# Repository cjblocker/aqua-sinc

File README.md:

# AquaSinc

A small home-made aquarium controller built around an ARM Cortex M4 STM32f and a Raspberry Pi

## Reference

- 1Bitsy Pinout [ https://github.com/esden/1BitSy ]

## Parts
- 3.3V LDO [ https://www.arrow.com/en/products/mcp1703a-3302edb/microchip-technology ]
- Green Chip LED [ https://www.arrow.com/en/products/kpg-1608vgc-a/kingbright ]

## Dev Instructions for Black Magic Probe

Putting these here because I forget...

1. `$ arm-none-eabi-gdb src/main.elf` or `make debug`
    Upon start up of gdb, these should automatically be exectured from .gdbinit
    ```bash
    (gdb) set target-async on
    (gdb) set confirm off
    (gdb) set mem inaccessible-by-default off
    (gdb) target extended-remote /dev/cu.usbmodem7BAB88A81
    (gdb) monitor version
    (gdb) monitor swdp_scan
    (gdb) attach 1
    ```
2. Load the program from the connected computer with `load`
3. Use any of the following to debug
    * `run` - start or restart the program
    * `start` - run till the beginning of the main function, restart if needed
    * `Ctrl-C` - interrupt the program while running
    * `continue` - resume running after being stopped
    * `next` - run next line of program (but don't step into functions)
    * `step` - like next, but steps into a function
    * `finish` - run till you leave the current function
    * `list [line number]` - show 10 lines surrounding [line number], current line by default
    * `info locals` - print out local variables
    * `set variable <var_name>=<value>` - set variable _var_name_ to _value_
    * `break <line_number>` - set a breakpoint at _line_number_
    * `info breakpoints` - list current breakpoints
    * `disable breakpoints`
    * `delete breakpoints`
    * `watch <var_name>` - set a watchpoint on variable _var_name_
    * `print <expression>` - evaluates expression and prints it
    * `printf <format_string>,<var_name>` - place _var_name_ in the format string at points with %d,%s,etc
    * `commands ... end` - execute the given commands after the previously created watchpoint is changed. 
        Example:
        ```bash
        (gdb) watch blink_count
        (gdb) commands
        > printf "blink extend condition %d\n", blink_count^4
        > end
        ```
4. If you make changes to main.c, you can run make from within gdb, followed by `load`.
5. `quit` to exit gdb or `Ctrl-D`

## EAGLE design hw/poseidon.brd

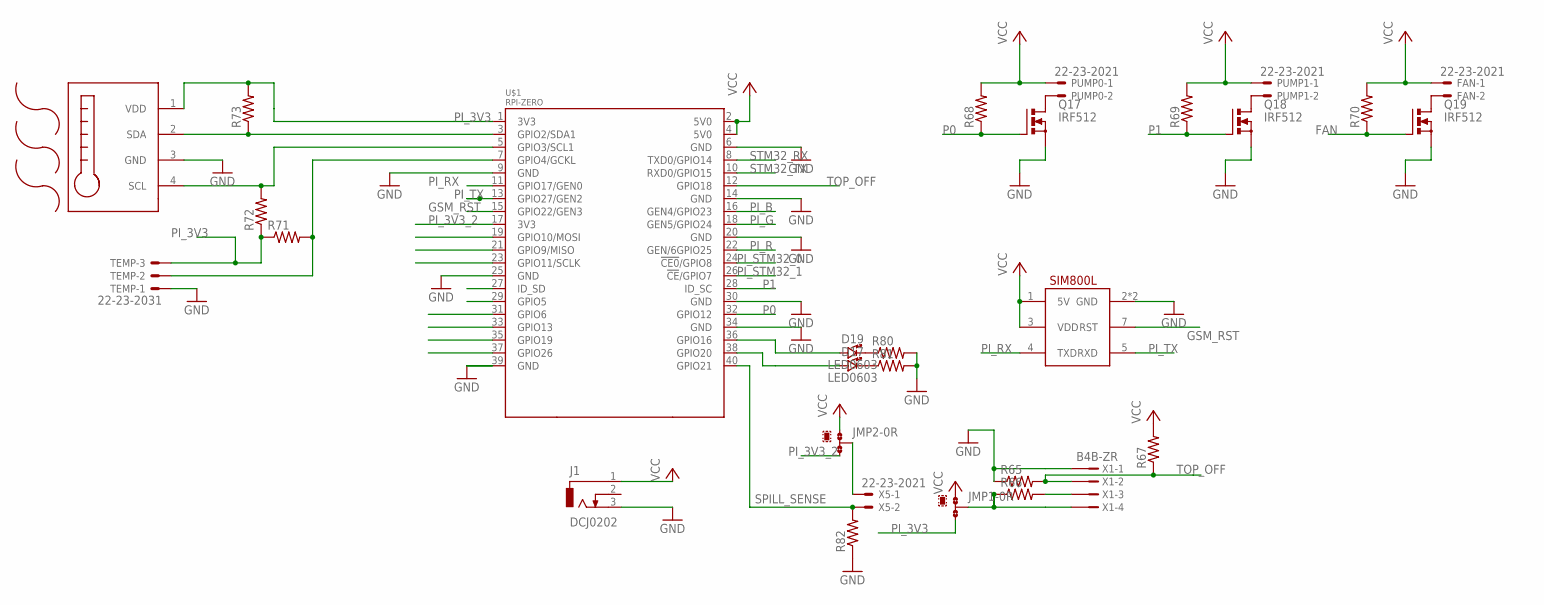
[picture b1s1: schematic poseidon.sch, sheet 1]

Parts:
D17, D19: LED0603; LED-0603
FAN: 22-23-2021
J1: DCJ0202
JMP1, JMP2: 0R-JUMPA; A0R-JMP
PUMP0, PUMP1: 22-23-2021
Q17, Q18, Q19: IRF512; TO220BV
R65, R66, R68, R69, R70, R71, R72, R73, R80, R81, R82: R-US_R0805; R0805
R67: R-US_M0805; M0805
TEMP: 22-23-2031
U$1: RPI-ZERO; RASPBERRYPI_BASTELSTUBE_V13_RASPI_BOARD_B+_FULL
U$3: AM2320; 4PIN_SMD
U$21: SIM800L; SIP
X1: B4B-ZR
X5: 22-23-2021

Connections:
FAN: Q19.G, R70.1; also elsewhere on the board
GND: J1.3, Q17.S, Q18.S, Q19.S, R65.1, R80.2, R81.2, R82.1, TEMP.1, U$1.6 (GND), U$1.9 (GND), U$1.14 (GND), U$1.20 (GND), U$1.25 (GND), U$1.30 (GND), U$1.34 (GND), U$1.39 (GND), U$3.3 (GND), U$21.2 (GND), U$21.6 (GND), X1.1; also elsewhere on the board
GSM_RST: U$1.15 (GPIO22/GEN3), U$21.7 (RST)
unnamed: PUMP0.2, Q17.D
unnamed: D19.C (CATHODE), R80.1
unnamed: R66.2, X1.3
unnamed: JMP1.2, R66.1, X1.4
unnamed: PUMP1.2, Q18.D
unnamed: D17.C (CATHODE), R81.1
unnamed: FAN.2, Q19.D
unnamed: R71.2, TEMP.2, U$1.7 (GPIO4/GCKL)
unnamed: R73.1, U$1.3 (GPIO2/SDA1), U$3.2 (SDA)
unnamed: R72.2, U$1.5 (GPIO3/SCL1), U$3.4 (SCL)
unnamed: D19.A (ANODE), U$1.36 (GPIO16)
unnamed: D17.A (ANODE), U$1.38 (GPIO20)
unnamed: JMP2.2, X5.1
P0: Q17.G, R68.1, U$1.32 (GPIO12)
P1: Q18.G, R69.1, U$1.28 (ID_SC)
PI_3V3: JMP1.3, R71.1, R72.1, R73.2, TEMP.3, U$1.1 (3V3), U$3.1 (VDD); also elsewhere on the board
PI_3V3_2: JMP2.3, U$1.17 (3V3)
PI_B: U$1.16 (GEN4/GPIO23); also elsewhere on the board
PI_G: U$1.18 (GEN5/GPIO24); also elsewhere on the board
PI_R: U$1.22 (GEN/6GPIO25); also elsewhere on the board
PI_RX: U$1.11 (GPIO17/GEN0), U$21.4 (TXD)
PI_STM32_0: U$1.24 (!CE0!/GPIO8); also elsewhere on the board
PI_STM32_1: U$1.26 (!CE!/GPIO7); also elsewhere on the board
PI_TX: U$1.13 (GPIO27/GEN2), U$21.5 (RXD)
SPILL_SENSE: R82.2, U$1.40 (GPIO21), X5.2
STM32_RX: U$1.8 (TXD0/GPIO14); also elsewhere on the board
STM32_TX: U$1.10 (RXD0/GPIO15); also elsewhere on the board
TOP_OFF: R65.2, R67.1, U$1.12 (GPIO18), X1.2
VCC: FAN.1, J1.1, JMP1.1, JMP2.1, PUMP0.1, PUMP1.1, R67.2, R68.2, R69.2, R70.2, U$1.2 (5V0), U$1.4 (5V0), U$21.1 (5V), U$21.3 (VDD); also elsewhere on the board

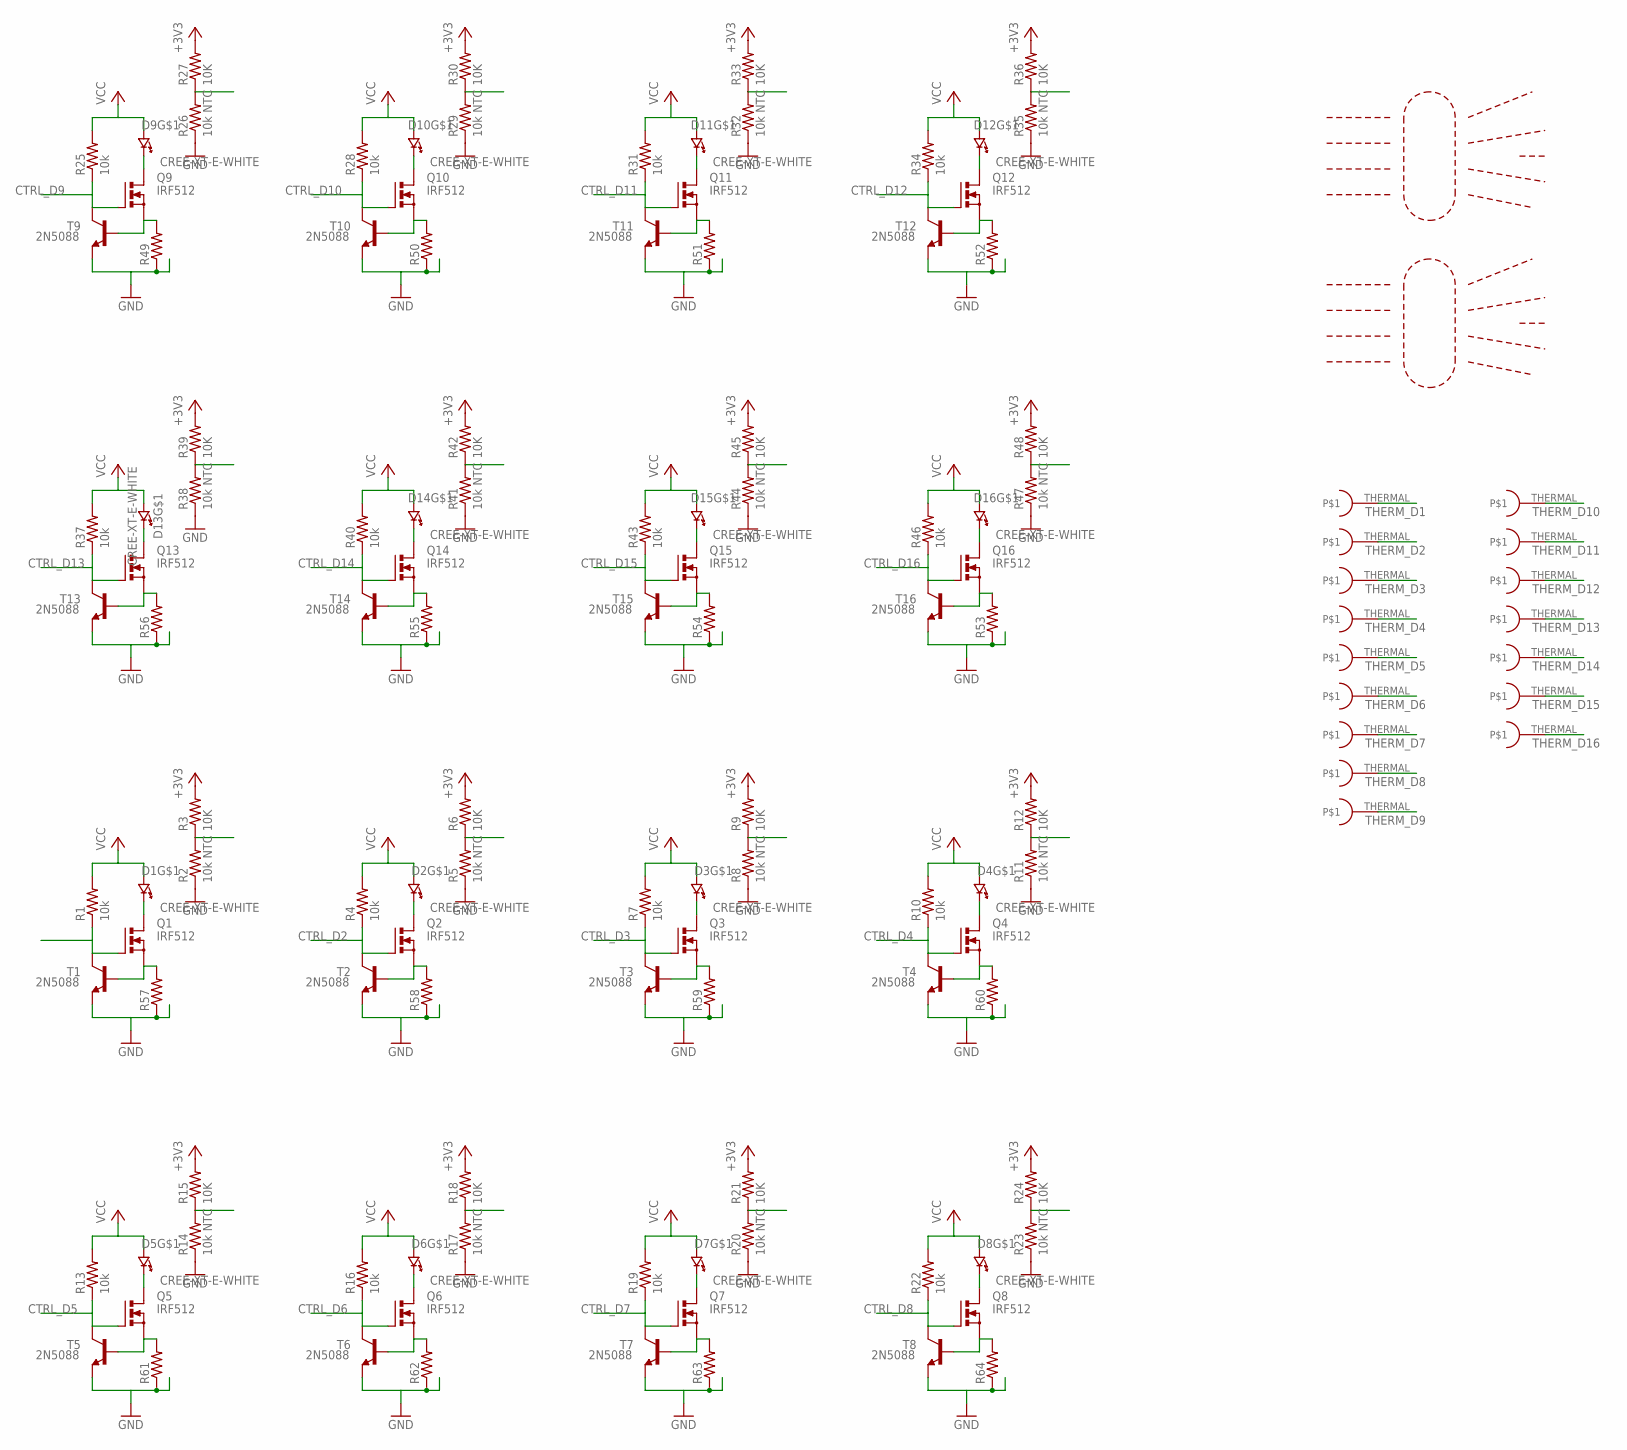
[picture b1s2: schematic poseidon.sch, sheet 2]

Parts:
D1, D2, D3, D4, D5, D6, D7, D8, D9, D10, D11, D12, D13, D14, D15, D16: CREE-XT-E-WHITE; CREE-XT-E
Q1, Q2, Q3, Q4, Q5, Q6, Q7, Q8, Q9, Q10, Q11, Q12, Q13, Q14, Q15, Q16: IRF512; TO220BV
R1, R4, R7, R10, R13, R16, R19, R22, R25, R28, R31, R34, R37, R40, R43, R46: 10k; R0805
R2, R5, R8, R11, R14, R17, R20, R23, R26, R29, R32, R35, R38, R41, R44, R47: 10k NTC; R0805
R3, R6, R9, R12, R15, R18, R21, R24, R27, R30, R33, R36, R39, R42, R45, R48: 10K; R0603
R49, R50, R51, R52, R53, R54, R55, R56, R57, R58, R59, R60, R61, R62, R63, R64: R-US_R2512; R2512
T1, T2, T3, T4, T5, T6, T7, T8, T9, T10, T11, T12, T13, T14, T15, T16: 2N5088; TO92
U$19, U$20: 8X_LED_OPTIC; FOCUS_GRID

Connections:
+3V3: R3.2, R6.2, R9.2, R12.2, R15.2, R18.2, R21.2, R24.2, R27.2, R30.2, R33.2, R36.2, R39.2, R42.2, R45.2, R48.2; also elsewhere on the board
CTRL_D1: Q1.G, R1.1, T1.1 (C); also elsewhere on the board
CTRL_D2: Q2.G, R4.1, T2.1 (C); also elsewhere on the board
CTRL_D3: Q3.G, R7.1, T3.1 (C); also elsewhere on the board
CTRL_D4: Q4.G, R10.1, T4.1 (C); also elsewhere on the board
CTRL_D5: Q5.G, R13.1, T5.1 (C); also elsewhere on the board
CTRL_D6: Q6.G, R16.1, T6.1 (C); also elsewhere on the board
CTRL_D7: Q7.G, R19.1, T7.1 (C); also elsewhere on the board
CTRL_D8: Q8.G, R22.1, T8.1 (C); also elsewhere on the board
CTRL_D9: Q9.G, R25.1, T9.1 (C); also elsewhere on the board
CTRL_D10: Q10.G, R28.1, T10.1 (C); also elsewhere on the board
CTRL_D11: Q11.G, R31.1, T11.1 (C); also elsewhere on the board
CTRL_D12: Q12.G, R34.1, T12.1 (C); also elsewhere on the board
CTRL_D13: Q13.G, R37.1, T13.1 (C); also elsewhere on the board
CTRL_D14: Q14.G, R40.1, T14.1 (C); also elsewhere on the board
CTRL_D15: Q15.G, R43.1, T15.1 (C); also elsewhere on the board
CTRL_D16: Q16.G, R46.1, T16.1 (C); also elsewhere on the board
GND: R2.1, R5.1, R8.1, R11.1, R14.1, R17.1, R20.1, R23.1, R26.1, R29.1, R32.1, R35.1, R38.1, R41.1, R44.1, R47.1, R49.1, R50.1, R51.1, R52.1, R53.1, R54.1, R55.1, R56.1, R57.1, R58.1, R59.1, R60.1, R61.1, R62.1, R63.1, R64.1, T1.3 (E), T2.3 (E), T3.3 (E), T4.3 (E), T5.3 (E), T6.3 (E), T7.3 (E), T8.3 (E), T9.3 (E), T10.3 (E), T11.3 (E), T12.3 (E), T13.3 (E), T14.3 (E), T15.3 (E), T16.3 (E); also elsewhere on the board
unnamed: D1.K (CATHODE), Q1.D
unnamed: Q1.S, R57.2, T1.2 (B)
unnamed: D2.K (CATHODE), Q2.D
unnamed: Q2.S, R58.2, T2.2 (B)
unnamed: D3.K (CATHODE), Q3.D
unnamed: Q3.S, R59.2, T3.2 (B)
unnamed: D4.K (CATHODE), Q4.D
unnamed: Q4.S, R60.2, T4.2 (B)
unnamed: D5.K (CATHODE), Q5.D
unnamed: Q5.S, R61.2, T5.2 (B)
unnamed: D6.K (CATHODE), Q6.D
unnamed: Q6.S, R62.2, T6.2 (B)
unnamed: D7.K (CATHODE), Q7.D
unnamed: Q7.S, R63.2, T7.2 (B)
unnamed: D8.K (CATHODE), Q8.D
unnamed: Q8.S, R64.2, T8.2 (B)
unnamed: D9.K (CATHODE), Q9.D
unnamed: Q9.S, R49.2, T9.2 (B)
unnamed: D10.K (CATHODE), Q10.D
unnamed: Q10.S, R50.2, T10.2 (B)
unnamed: D11.K (CATHODE), Q11.D
unnamed: Q11.S, R51.2, T11.2 (B)
unnamed: D12.K (CATHODE), Q12.D
unnamed: Q12.S, R52.2, T12.2 (B)
unnamed: D13.K (CATHODE), Q13.D
unnamed: Q13.S, R56.2, T13.2 (B)
unnamed: D14.K (CATHODE), Q14.D
unnamed: Q14.S, R55.2, T14.2 (B)
unnamed: D15.K (CATHODE), Q15.D
unnamed: Q15.S, R54.2, T15.2 (B)
unnamed: D16.K (CATHODE), Q16.D
unnamed: Q16.S, R53.2, T16.2 (B)
TEMP_D1: R41.2, R42.1; also elsewhere on the board
TEMP_D2: R8.2, R9.1; also elsewhere on the board
TEMP_D3: R14.2, R15.1; also elsewhere on the board
TEMP_D4: R17.2, R18.1; also elsewhere on the board
TEMP_D5: R44.2, R45.1; also elsewhere on the board
TEMP_D6: R47.2, R48.1; also elsewhere on the board
TEMP_D7: R11.2, R12.1; also elsewhere on the board
TEMP_D8: R20.2, R21.1; also elsewhere on the board
TEMP_D9: R32.2, R33.1; also elsewhere on the board
TEMP_D10: R29.2, R30.1; also elsewhere on the board
TEMP_D11: R26.2, R27.1; also elsewhere on the board
TEMP_D12: R23.2, R24.1; also elsewhere on the board
TEMP_D13: R5.2, R6.1; also elsewhere on the board
TEMP_D14: R35.2, R36.1; also elsewhere on the board
TEMP_D15: R38.2, R39.1; also elsewhere on the board
TEMP_D16: R2.2, R3.1; also elsewhere on the board
THERM_D1: D1.THERMAL
THERM_D2: D2.THERMAL
THERM_D3: D3.THERMAL
THERM_D4: D4.THERMAL
THERM_D5: D5.THERMAL
THERM_D6: D6.THERMAL
THERM_D7: D7.THERMAL
THERM_D8: D8.THERMAL
THERM_D9: D9.THERMAL
THERM_D10: D10.THERMAL
THERM_D11: D11.THERMAL
THERM_D12: D12.THERMAL
THERM_D13: D13.THERMAL
THERM_D14: D14.THERMAL
THERM_D15: D15.THERMAL
THERM_D16: D16.THERMAL
VCC: D1.A (ANODE), D2.A (ANODE), D3.A (ANODE), D4.A (ANODE), D5.A (ANODE), D6.A (ANODE), D7.A (ANODE), D8.A (ANODE), D9.A (ANODE), D10.A (ANODE), D11.A (ANODE), D12.A (ANODE), D13.A (ANODE), D14.A (ANODE), D15.A (ANODE), D16.A (ANODE), R1.2, R4.2, R7.2, R10.2, R13.2, R16.2, R19.2, R22.2, R25.2, R28.2, R31.2, R34.2, R37.2, R40.2, R43.2, R46.2; also elsewhere on the board

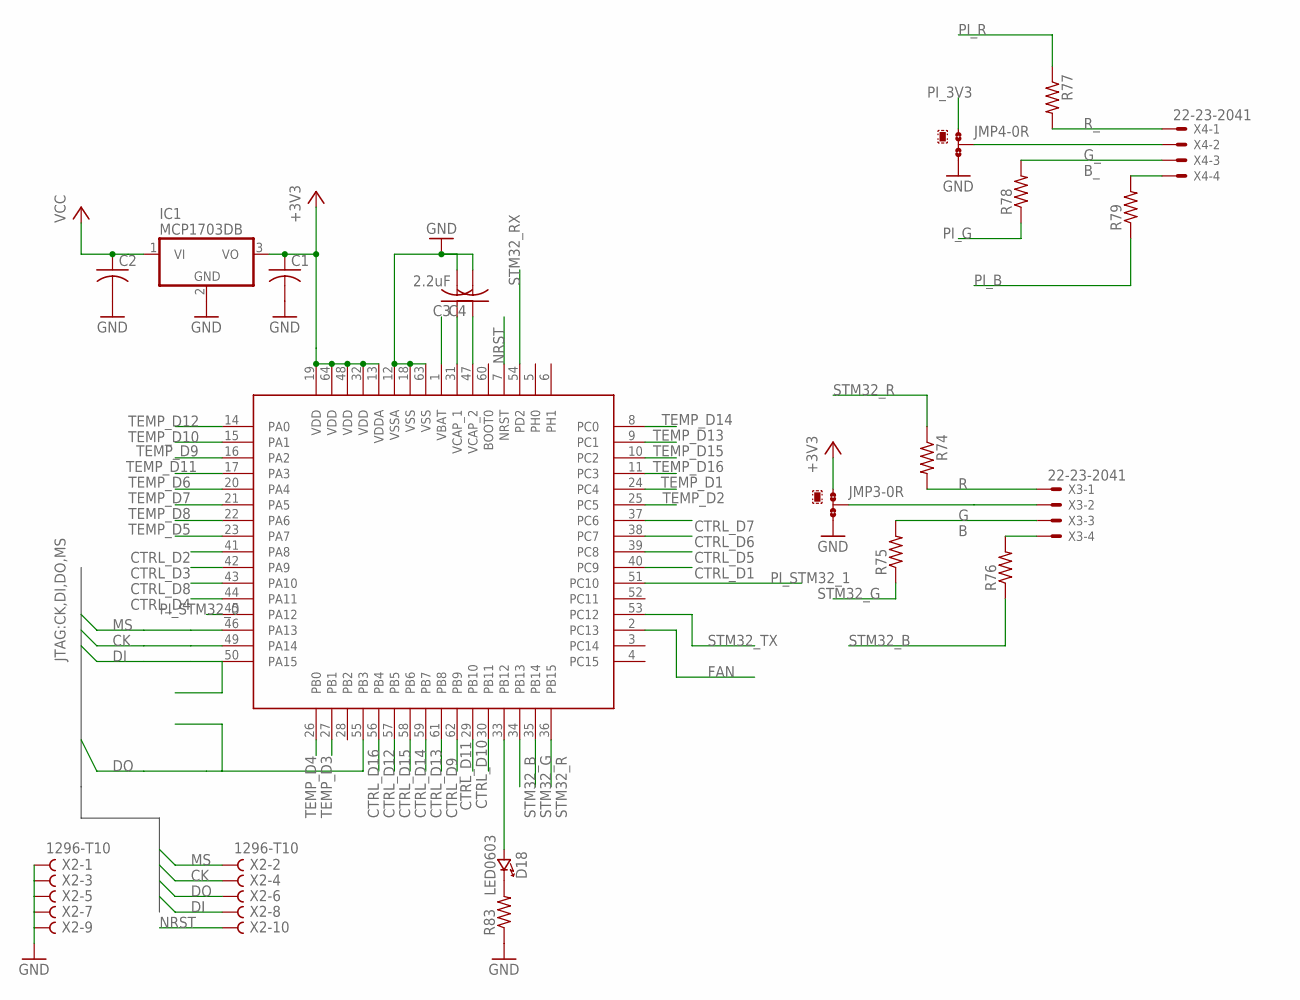
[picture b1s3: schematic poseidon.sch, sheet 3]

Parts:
C1, C2: C-USC0805; C0805
C3: 2.2uF; C0402K
C4: C-USC0402K; C0402K
D18: LED0603; LED-0603
IC1: MCP1703DB; SOT223
JMP3, JMP4: 0R-JUMPA; A0R-JMP
R74, R75, R76, R77, R78, R79, R83: R-US_R0805; R0805
U$2: STM32F41; QFP50P1200X1200X160-64
X2: 1296-T10; 1296-10
X3, X4: 22-23-2041

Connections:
+3V3: C1.1, IC1.3 (VO), JMP3.1, U$2.13 (VDDA), U$2.19 (VDD), U$2.32 (VDD), U$2.48 (VDD), U$2.64 (VDD); also elsewhere on the board
B: R76.2, X3.4
B_: R79.2, X4.4
CK: U$2.49 (PA14), X2.4
CTRL_D1: U$2.40 (PC9); also elsewhere on the board
CTRL_D2: U$2.41 (PA8); also elsewhere on the board
CTRL_D3: U$2.42 (PA9); also elsewhere on the board
CTRL_D4: U$2.44 (PA11); also elsewhere on the board
CTRL_D5: U$2.39 (PC8); also elsewhere on the board
CTRL_D6: U$2.38 (PC7); also elsewhere on the board
CTRL_D7: U$2.37 (PC6); also elsewhere on the board
CTRL_D8: U$2.43 (PA10); also elsewhere on the board
CTRL_D9: U$2.62 (PB9); also elsewhere on the board
CTRL_D10: U$2.30 (PB11); also elsewhere on the board
CTRL_D11: U$2.29 (PB10); also elsewhere on the board
CTRL_D12: U$2.57 (PB5); also elsewhere on the board
CTRL_D13: U$2.61 (PB8); also elsewhere on the board
CTRL_D14: U$2.59 (PB7); also elsewhere on the board
CTRL_D15: U$2.58 (PB6); also elsewhere on the board
CTRL_D16: U$2.56 (PB4); also elsewhere on the board
DI: U$2.50 (PA15), X2.8
DO: U$2.55 (PB3), X2.6
FAN: U$2.2 (PC13); also elsewhere on the board
G: R75.2, X3.3
GND: C1.2, C2.2, C3.2, C4.2, IC1.2 (GND), JMP3.3, JMP4.3, R83.1, U$2.12 (VSSA), U$2.18 (VSS), U$2.63 (VSS), X2.1, X2.3, X2.5, X2.7, X2.9; also elsewhere on the board
G_: R78.2, X4.3
MS: U$2.46 (PA13), X2.2
unnamed: JMP4.2, X4.2
unnamed: JMP3.2, X3.2
unnamed: D18.C (CATHODE), R83.2
unnamed: D18.A (ANODE), U$2.33 (PB12)
unnamed: C3.1, U$2.31 (VCAP_1)
unnamed: C4.1, U$2.47 (VCAP_2)
NRST: U$2.7 (NRST), X2.10
PI_3V3: JMP4.1; also elsewhere on the board
PI_B: R79.1; also elsewhere on the board
PI_G: R78.1; also elsewhere on the board
PI_R: R77.1; also elsewhere on the board
PI_STM32_0: U$2.45 (PA12); also elsewhere on the board
PI_STM32_1: U$2.51 (PC10); also elsewhere on the board
R: R74.2, X3.1
R_: R77.2, X4.1
STM32_B: R76.1, U$2.34 (PB13)
STM32_G: R75.1, U$2.35 (PB14)
STM32_R: R74.1, U$2.36 (PB15)
STM32_RX: U$2.54 (PD2); also elsewhere on the board
STM32_TX: U$2.53 (PC12); also elsewhere on the board
TEMP_D1: U$2.24 (PC4); also elsewhere on the board
TEMP_D2: U$2.25 (PC5); also elsewhere on the board
TEMP_D3: U$2.27 (PB1); also elsewhere on the board
TEMP_D4: U$2.26 (PB0); also elsewhere on the board
TEMP_D5: U$2.23 (PA7); also elsewhere on the board
TEMP_D6: U$2.20 (PA4); also elsewhere on the board
TEMP_D7: U$2.21 (PA5); also elsewhere on the board
TEMP_D8: U$2.22 (PA6); also elsewhere on the board
TEMP_D9: U$2.16 (PA2); also elsewhere on the board
TEMP_D10: U$2.15 (PA1); also elsewhere on the board
TEMP_D11: U$2.17 (PA3); also elsewhere on the board
TEMP_D12: U$2.14 (PA0); also elsewhere on the board
TEMP_D13: U$2.9 (PC1); also elsewhere on the board
TEMP_D14: U$2.8 (PC0); also elsewhere on the board
TEMP_D15: U$2.10 (PC2); also elsewhere on the board
TEMP_D16: U$2.11 (PC3); also elsewhere on the board
VCC: C2.1, IC1.1 (VI); also elsewhere on the board

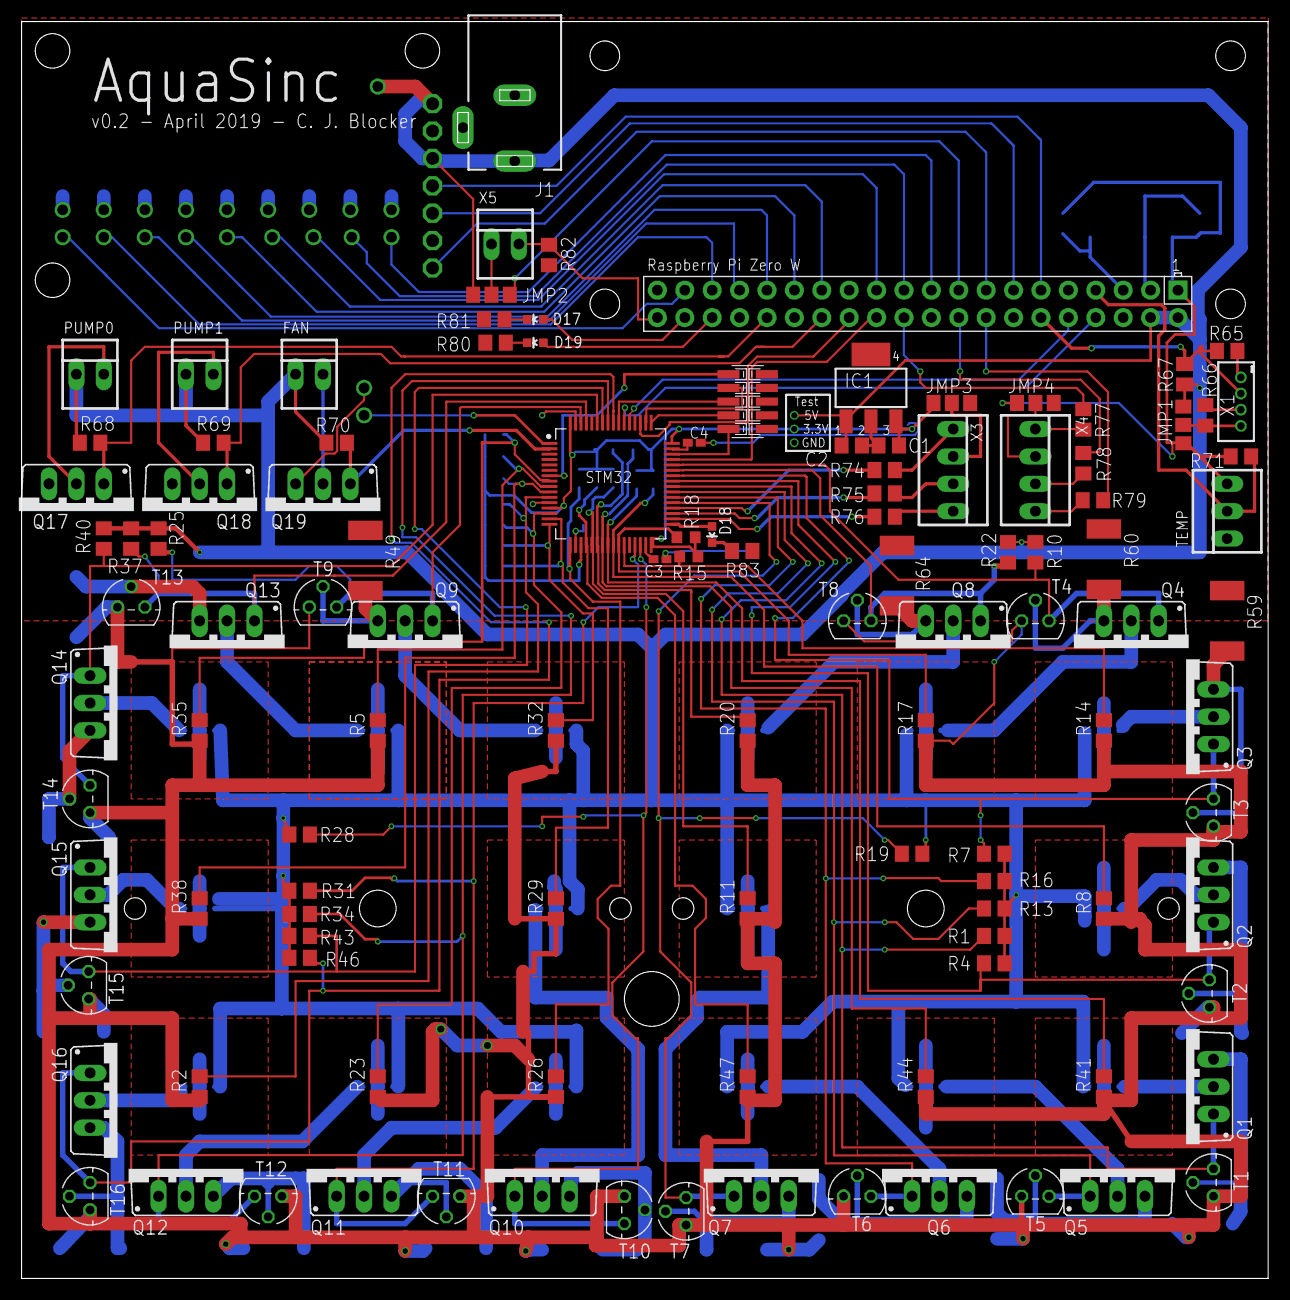
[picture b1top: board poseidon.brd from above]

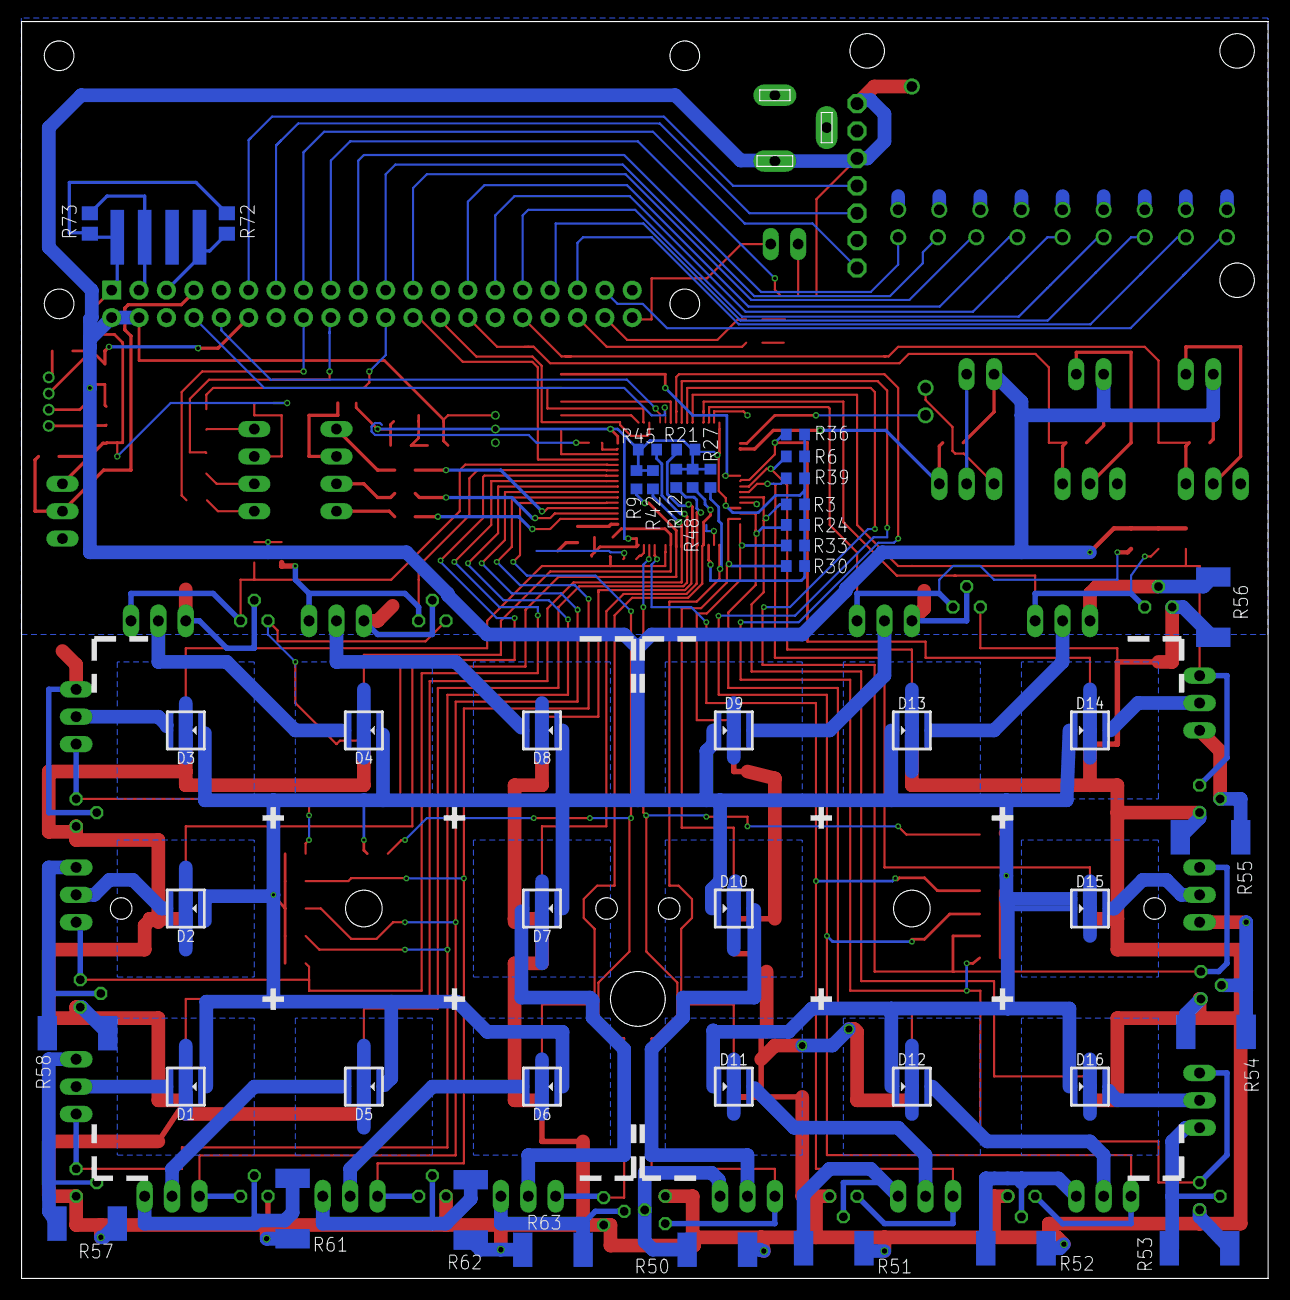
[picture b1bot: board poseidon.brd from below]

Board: 2 copper layers, 115.5 x 116.5 mm, 162 parts (47 on the bottom side), 117 nets.

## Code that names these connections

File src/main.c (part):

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#include <stdint.h>
#include <stdio.h>

static const adc_channel temp0 = { // PA0, ADC1 channel 0
    .adc_adc = ADC1,
    .adc_channel = 0,
    .adc_gpio = {
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    },
};

static const adc_channel temp1 = { // PA1, ADC1 channel 1
    .adc_adc = ADC1,
    .adc_channel = 1,
    .adc_gpio = {
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    },
};

static const adc_channel temp2 = { // PA2, ADC1 channel 2
    .adc_adc = ADC1,
    .adc_channel = 2,
    .adc_gpio = {
        .gp_port   = GPIOA,
        .gp_pin    = GPIO2,
        .gp_mode   = GPIO_MODE_ANALOG,
        .gp_pupd   = GPIO_PUPD_NONE,
        .gp_af     = 0,
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    },
};

static const adc_channel temp3 = { // PA3, ADC1 channel 3
    .adc_adc = ADC1,
    .adc_channel = 3,
    .adc_gpio = {
        .gp_port   = GPIOA,
        .gp_pin    = GPIO3,
        .gp_mode   = GPIO_MODE_ANALOG,
        .gp_pupd   = GPIO_PUPD_NONE,
        .gp_af     = 0,
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    },
};

static const adc_channel temp4 = { // PA4, ADC1 channel 4
    .adc_adc = ADC1,
    .adc_channel = 4,
    .adc_gpio = {
        .gp_port   = GPIOA,
        .gp_pin    = GPIO4,
        .gp_mode   = GPIO_MODE_ANALOG,
        .gp_pupd   = GPIO_PUPD_NONE,
        .gp_af     = 0,
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    },
};

static const adc_channel temp5 = { // PA5, ADC1 channel 5
    .adc_adc = ADC1,
    .adc_channel = 5,
    .adc_gpio = {
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    },
};

static const adc_channel temp6 = { // PA6, ADC1 channel 6
    .adc_adc = ADC1,
    .adc_channel = 6,
    .adc_gpio = {
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    },
};

static const adc_channel temp7 = { // PA7, ADC1 channel 7
    .adc_adc = ADC1,
    .adc_channel = 7,
    .adc_gpio = {
        .gp_port   = GPIOA,
        .gp_pin    = GPIO7,
        .gp_mode   = GPIO_MODE_ANALOG,
        .gp_pupd   = GPIO_PUPD_NONE,
        .gp_af     = 0,
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    },
};

static const adc_channel temp8 = { // PB0, ADC1 channel 8
    .adc_adc = ADC1,
    .adc_channel = 8,
    .adc_gpio = {
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    },
};

static const adc_channel temp9 = { // PB1, ADC1 channel 9
    .adc_adc = ADC1,
    .adc_channel = 9,
    .adc_gpio = {
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    },
};

static const adc_channel temp10 = { // PC0, ADC1 channel 10
    .adc_adc = ADC1,
    .adc_channel = 10,
    .adc_gpio = {
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    },
};

static const adc_channel temp11 = { // PC1, ADC1 channel 11
    .adc_adc = ADC1,
    .adc_channel = 11,
    .adc_gpio = {
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    },
};

static const adc_channel temp12 = { // PC2, ADC1 channel 12
    .adc_adc = ADC1,
    .adc_channel = 12,
    .adc_gpio = {
        .gp_port   = GPIOC,
        .gp_pin    = GPIO2,
        .gp_mode   = GPIO_MODE_ANALOG,
        .gp_pupd   = GPIO_PUPD_NONE,
        .gp_af     = 0,
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    },
};

static const adc_channel temp13 = { // PC3, ADC1 channel 13
    .adc_adc = ADC1,
    .adc_channel = 13,
    .adc_gpio = {
        .gp_port   = GPIOC,
        .gp_pin    = GPIO3,
        .gp_mode   = GPIO_MODE_ANALOG,
        .gp_pupd   = GPIO_PUPD_NONE,
        .gp_af     = 0,
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    },
};

static const adc_channel temp14 = { // PC4, ADC1 channel 14
    .adc_adc = ADC1,
    .adc_channel = 14,
    .adc_gpio = {
        .gp_port   = GPIOC,
        .gp_pin    = GPIO4,
        .gp_mode   = GPIO_MODE_ANALOG,
        .gp_pupd   = GPIO_PUPD_NONE,
        .gp_af     = 0,
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    },
};

static const adc_channel temp15 = { // PC5, ADC1 channel 15
    .adc_adc = ADC1,
    .adc_channel = 15,
    .adc_gpio = {
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static void gpio_setup(void)
{
	/*
	 * Set GPIO8 (in GPIO port A) to
	 * 'output alternate function push-pull'.
	 */

	// PORT A

	// A8 - AF1 - T1 C1
	gpio_mode_setup(GPIOA, GPIO_MODE_AF, GPIO_PUPD_NONE, GPIO8);
  	gpio_set_af(GPIOA, GPIO_AF1, GPIO8);

	// A9 - AF1 - T1 C2
	gpio_mode_setup(GPIOA, GPIO_MODE_AF, GPIO_PUPD_NONE, GPIO9);
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  	// PORT B

  	// B4 - AF2 - T3 C1
	gpio_mode_setup(GPIOB, GPIO_MODE_AF, GPIO_PUPD_NONE, GPIO4);
  	gpio_set_af(GPIOB, GPIO_AF2, GPIO4);

  	// B5 - AF2 - T3 C2
	gpio_mode_setup(GPIOB, GPIO_MODE_AF, GPIO_PUPD_NONE, GPIO5);
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  	gpio_set_af(GPIOB, GPIO_AF2, GPIO6);

  	// B7 - AF2 - T4 C2
	gpio_mode_setup(GPIOB, GPIO_MODE_AF, GPIO_PUPD_NONE, GPIO7);
  	gpio_set_af(GPIOB, GPIO_AF2, GPIO7);

  	// B8 - AF2 - T4 C3
	gpio_mode_setup(GPIOB, GPIO_MODE_AF, GPIO_PUPD_NONE, GPIO8);
  	gpio_set_af(GPIOB, GPIO_AF2, GPIO8);

  	// B9 - AF2 - T4 C4
	gpio_mode_setup(GPIOB, GPIO_MODE_AF, GPIO_PUPD_NONE, GPIO9);
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  	gpio_set_af(GPIOC, GPIO_AF3, GPIO6);

  	// C7 - AF3 - T8 C2
	gpio_mode_setup(GPIOC, GPIO_MODE_AF, GPIO_PUPD_NONE, GPIO7);
  	gpio_set_af(GPIOC, GPIO_AF3, GPIO7);

  	// C8 - AF3 - T8 C3
	gpio_mode_setup(GPIOC, GPIO_MODE_AF, GPIO_PUPD_NONE, GPIO8);
  	gpio_set_af(GPIOC, GPIO_AF3, GPIO8);

  	// C9 - AF3 - T8 C4
	gpio_mode_setup(GPIOC, GPIO_MODE_AF, GPIO_PUPD_NONE, GPIO9);
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
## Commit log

2018-12-27 Ready for PWM channel tests
2018-12-29 Added UART and ADC functionality
    C11 ended up not being connected to ADC channel 11
    and had to be moved to C1
2019-03-04 First Board Revision Made
2019-03-31 Added process to use black magic probe to README.
2019-03-31 Fixed problems with first revision, including barrel jack polarity
    Also tidied up labels, connected extra vias to ground, created
    test points for power rails. Still need to fix water level sensor
    connector, which is currently too small.
